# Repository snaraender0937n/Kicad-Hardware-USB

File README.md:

# 🔌 KiCad Hardware Design Project

## 🔍 Overview
This repository contains an **open-source hardware design project created using KiCad**, including complete **schematic diagrams**, **PCB layout**, and **manufacturing-ready outputs**.  
It is intended for **learning, reference, and practical PCB prototyping**.

---

## 🛠️ Tools Used
🧰 KiCad (Version 7 or later)
🖼️ PCB Editor
🔷 3D Viewer
---

## 🖼️ PCB Preview
### 🔷 3D View

### 🔷 Top Layer

### 🔷 Bottom Layer

---

## 🗂️ Repository Structure
HARDWARE/ → KiCad schematic and PCB design files
IMAGES/ → Schematic, PCB layout, and 3D render images
BOM/ → Bill of Materials
GERBER/ → Manufacturing-ready Gerber files
---

## 🚀 How to Open the Project
1. Install **KiCad (v7 or later)**  
2. Clone this repository  
3. Open `USB_pro` using KiCad  

---

## 📦 Project Outputs
- ✅ Complete schematic design  
- ✅ PCB layout (top & bottom layers)  
- ✅ 3D PCB visualization  
- ✅ Bill of Materials (BOM)  
- ✅ Gerber files for PCB fabrication  

---

## 📄 License
📜 This project is licensed under the  
MIT LICENSE

---

## 👤 Author
**Naraender**  

---

## ⭐ Notes
If you find this repository useful, consider **starring ⭐ it** and using it as a reference for your own KiCad projects.

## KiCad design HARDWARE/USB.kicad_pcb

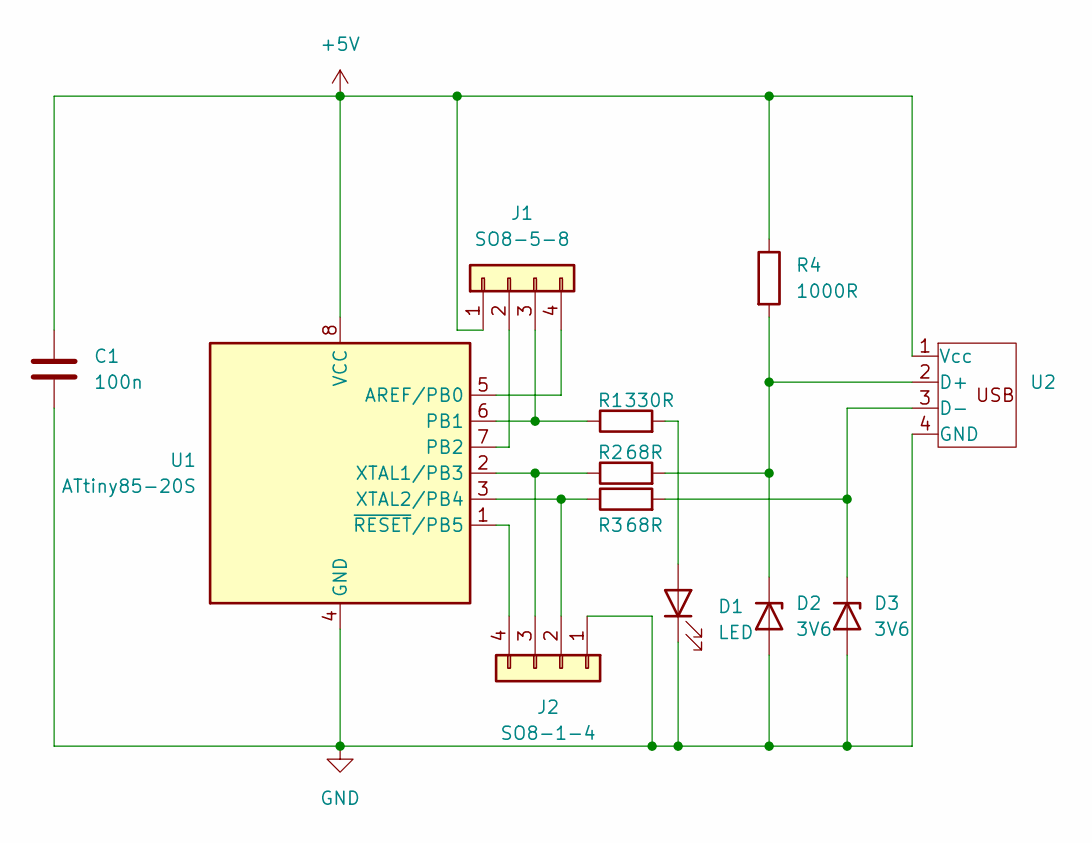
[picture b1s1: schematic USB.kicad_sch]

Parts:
C1: 100n; C_0603_1608Metric
D1: LED; LED_0603_1608Metric
D2, D3: 3V6; D_SOD-123
J1: SO8-5-8; PinHeader_1x04_P2.54mm_Horizontal
J2: SO8-1-4; PinHeader_1x04_P2.54mm_Horizontal
R1: 330R; R_0603_1608Metric
R2, R3: 68R; R_0603_1608Metric
R4: 1000R; R_0603_1608Metric
U1: ATtiny85-20S; SOIC-8_5.3x5.3mm_P1.27mm
U2: USB

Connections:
+5V: C1.1, J1.1, R4.1, U1.8 (VCC), U2.1 (Vcc)
GND: C1.2, D1.1 (K), D2.2 (A), D3.2 (A), J2.1, U1.4 (GND), U2.4 (GND)
unnamed: D1.2 (A), R1.2
unnamed: D2.1 (K), R2.2, R4.2, U2.2 (D+)
unnamed: D3.1 (K), R3.2, U2.3 (D-)
unnamed: J1.2, U1.7 (PB2)
unnamed: J1.3, R1.1, U1.6 (PB1)
unnamed: J1.4, U1.5 (AREF/PB0)
unnamed: J2.2, R3.1, U1.3 (XTAL2/PB4)
unnamed: J2.3, R2.1, U1.2 (XTAL1/PB3)
unnamed: J2.4, U1.1 (~RESET/PB5)

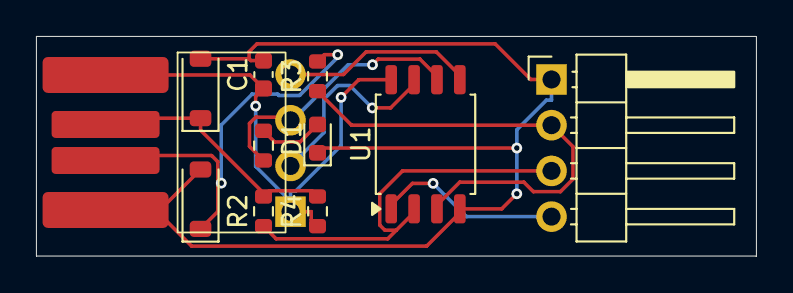
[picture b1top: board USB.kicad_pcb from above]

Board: 2 copper layers, 40.0 x 12.2 mm, 12 parts (1 on the bottom side), 11 nets.

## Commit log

2025-12-25 Add BOM CSV file with component details
2025-12-25 Create D
